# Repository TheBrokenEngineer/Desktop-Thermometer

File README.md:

# Desktop-Thermometer

A small desktop thermometer that just sits there and works. It acquires the ambient air temperature and shows the current temperature on 3 7-segment LED displays.

Designed to be low cost (under USD20) and be powered by a computer USB port, USB wall wart or power bank.

At the heart is a Microchip PIC16 microcontroller that reads the voltage produced by the sense pin on the TMP36/TMP37 sensor and shifts the converted value out to the display using 74HC595 shift registers. For full details of the device please refer to the documentation contained in the Documentation directory.

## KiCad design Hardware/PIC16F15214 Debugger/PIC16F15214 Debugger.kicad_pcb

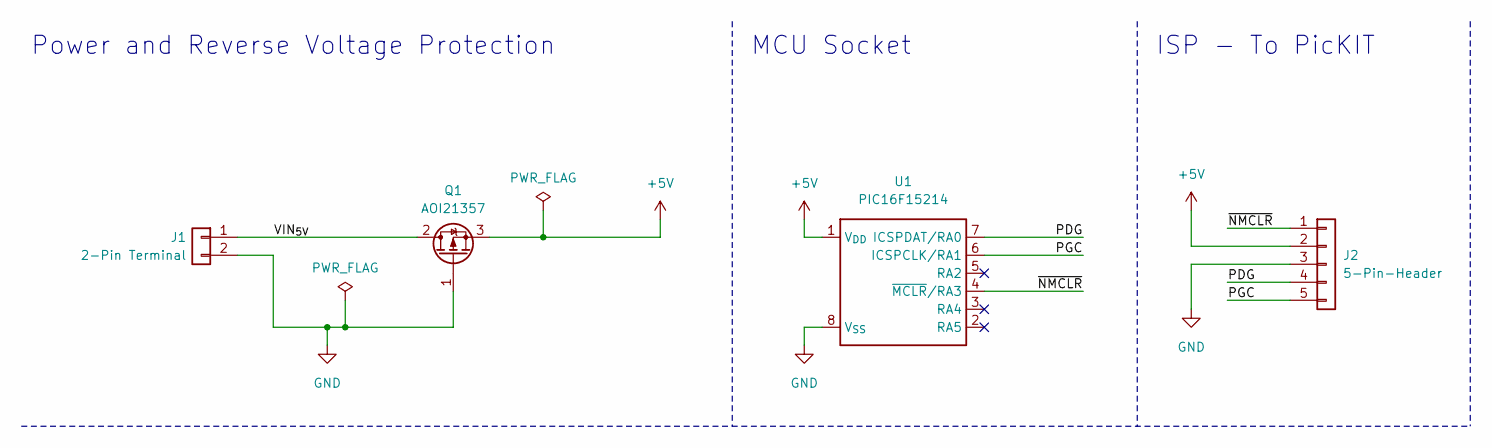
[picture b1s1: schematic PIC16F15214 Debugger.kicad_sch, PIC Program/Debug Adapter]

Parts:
J1: 2-Pin Terminal; Wurth 2 Pin Screwless Entry Wire to Board Connector
J2: 5-Pin-Header
Q1: AOI21357
U1: PIC16F15214; DIP-8_W7.62mm_Socket_Wire_Wrap

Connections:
+5V: J2.2, Q1.3 (S), U1.1 (V_{DD})
/PDG: J2.4, U1.7 (ICSPDAT/RA0)
/PGC: J2.5, U1.6 (ICSPCLK/RA1)
/VIN_{5V}: J1.1, Q1.2 (D)
/~NMCLR: J2.1, U1.4 (~MCLR/RA3)
GND: J1.2, J2.3, Q1.1 (G), U1.8 (V_{SS})

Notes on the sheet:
Power and Reverse Voltage Protection
ISP - To PicKIT
MCU Socket

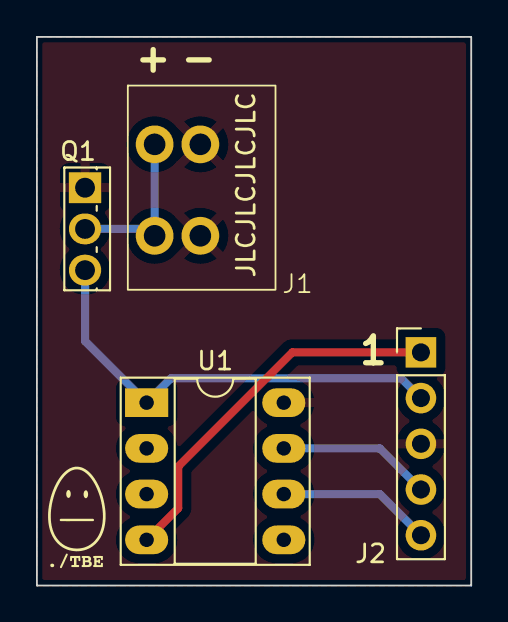
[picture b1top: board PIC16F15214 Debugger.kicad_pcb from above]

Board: 2 copper layers, 24.1 x 30.5 mm, 4 parts (0 on the bottom side), 6 nets.

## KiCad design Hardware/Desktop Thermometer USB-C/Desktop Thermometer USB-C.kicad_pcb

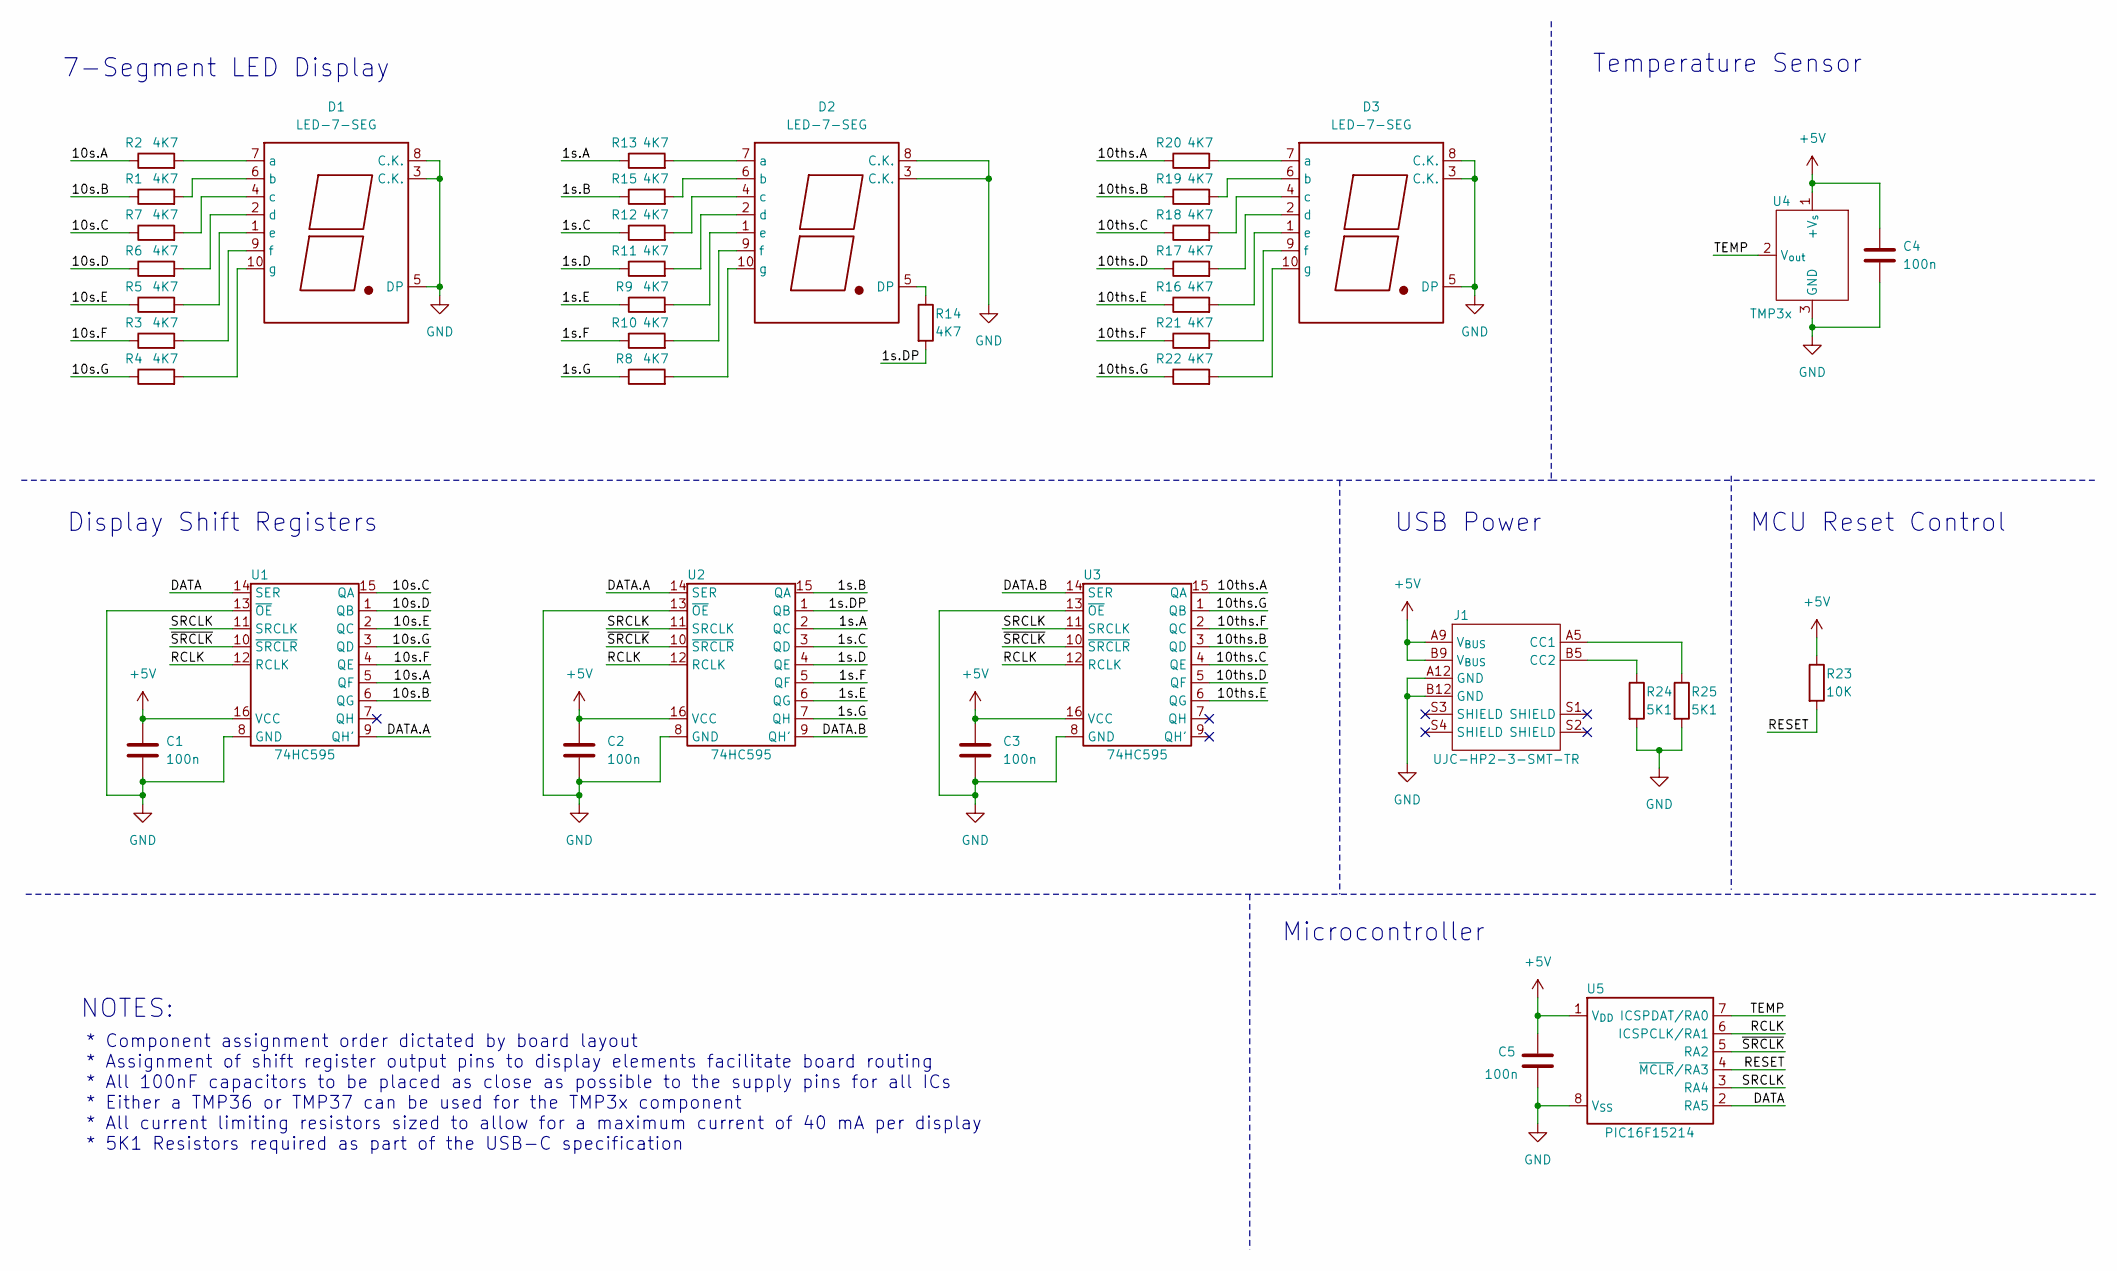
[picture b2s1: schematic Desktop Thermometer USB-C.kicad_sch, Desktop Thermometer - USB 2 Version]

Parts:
C1, C2, C3, C4, C5: 100n; C_Epoxy_D5.5mm_W3.2mm_P5.00mm
D1, D2, D3: LED-7-SEG
J1: UJC-HP2-3-SMT-TR; CUI_UJC-HP2-3-SMT-TR
R1, R2, R3, R4, R5, R6, R7, R8, R9, R10, R11, R12, R13, R14, R15, R16, R17, R18, R19, R20, R21, R22: 4K7; R_Axial_DIN0207_L6.3mm_D2.5mm_P10.16mm_Horizontal
R23: 10K; R_Axial_DIN0207_L6.3mm_D2.5mm_P10.16mm_Horizontal
R24, R25: 5K1; R_Axial_DIN0207_L6.3mm_D2.5mm_P10.16mm_Horizontal
U1, U2, U3: 74HC595; DIP-16_W7.62mm_LongPads
U4: TMP3x; TMP3x_TO-92
U5: PIC16F15214; DIP-8_W7.62mm_LongPads

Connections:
+5V: C1.1, C2.1, C3.1, C4.1, C5.1, J1.A9 (V_{BUS}), J1.B9 (V_{BUS}), R23.1, U1.16 (VCC), U2.16 (VCC), U3.16 (VCC), U4.1 (+V_{s}), U5.1 (V_{DD})
/1s.A: R13.1, U2.2 (QC)
/1s.B: R15.1, U2.15 (QA)
/1s.C: R12.1, U2.3 (QD)
/1s.D: R11.1, U2.4 (QE)
/1s.DP: R14.2, U2.1 (QB)
/1s.E: R9.1, U2.6 (QG)
/1s.F: R10.1, U2.5 (QF)
/1s.G: R8.1, U2.7 (QH)
/10s.A: R2.1, U1.5 (QF)
/10s.B: R1.1, U1.6 (QG)
/10s.C: R7.1, U1.15 (QA)
/10s.D: R6.1, U1.1 (QB)
/10s.E: R5.1, U1.2 (QC)
/10s.F: R3.1, U1.4 (QE)
/10s.G: R4.1, U1.3 (QD)
/10ths.A: R20.1, U3.15 (QA)
/10ths.B: R19.1, U3.3 (QD)
/10ths.C: R18.1, U3.4 (QE)
/10ths.D: R17.1, U3.5 (QF)
/10ths.E: R16.1, U3.6 (QG)
/10ths.F: R21.1, U3.2 (QC)
/10ths.G: R22.1, U3.1 (QB)
/DATA: U1.14 (SER), U5.2 (RA5)
/DATA.A: U1.9 (QH'), U2.14 (SER)
/DATA.B: U2.9 (QH'), U3.14 (SER)
/RCLK: U1.12 (RCLK), U2.12 (RCLK), U3.12 (RCLK), U5.6 (ICSPCLK/RA1)
/RESET: R23.2, U5.4 (~MCLR/RA3)
/SRCLK: U1.11 (SRCLK), U2.11 (SRCLK), U3.11 (SRCLK), U5.3 (RA4)
/TEMP: U4.2 (V_{out}), U5.7 (ICSPDAT/RA0)
/~SRCLK: U1.10 (~SRCLR), U2.10 (~SRCLR), U3.10 (~SRCLR), U5.5 (RA2)
GND: C1.2, C2.2, C3.2, C4.2, C5.2, D1.3 (C.K.), D1.5 (DP), D1.8 (C.K.), D2.3 (C.K.), D2.8 (C.K.), D3.3 (C.K.), D3.5 (DP), D3.8 (C.K.), J1.A12 (GND), J1.B12 (GND), R24.2, R25.2, U1.8 (GND), U1.13 (~OE), U2.8 (GND), U2.13 (~OE), U3.8 (GND), U3.13 (~OE), U4.3 (GND), U5.8 (V_{SS})
unnamed: D1.7 (a), R2.2
unnamed: D1.6 (b), R1.2
unnamed: D1.4 (c), R7.2
unnamed: D1.2 (d), R6.2
unnamed: D1.1 (e), R5.2
unnamed: D1.9 (f), R3.2
unnamed: D1.10 (g), R4.2
unnamed: D2.5 (DP), R14.1
unnamed: D2.7 (a), R13.2
unnamed: D2.6 (b), R15.2
unnamed: D2.4 (c), R12.2
unnamed: D2.2 (d), R11.2
unnamed: D2.1 (e), R9.2
unnamed: D2.9 (f), R10.2
unnamed: D2.10 (g), R8.2
unnamed: D3.7 (a), R20.2
unnamed: D3.6 (b), R19.2
unnamed: D3.4 (c), R18.2
unnamed: D3.2 (d), R17.2
unnamed: D3.1 (e), R16.2
unnamed: D3.9 (f), R21.2
unnamed: D3.10 (g), R22.2
unnamed: J1.A5 (CC1), R25.1
unnamed: J1.B5 (CC2), R24.1

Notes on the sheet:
Microcontroller
Temperature Sensor
USB Power
* Component assignment order dictated by board layout * Assignment of shift register output pins to display elements facilitate board routing * All 100nF capacitors to be placed as close as possible to the supply pins for all ICs * Either a TMP36 or TMP37 can be used for the TMP3x component * All c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
Display Shift Registers
NOTES:
7-Segment LED Display
MCU Reset Control

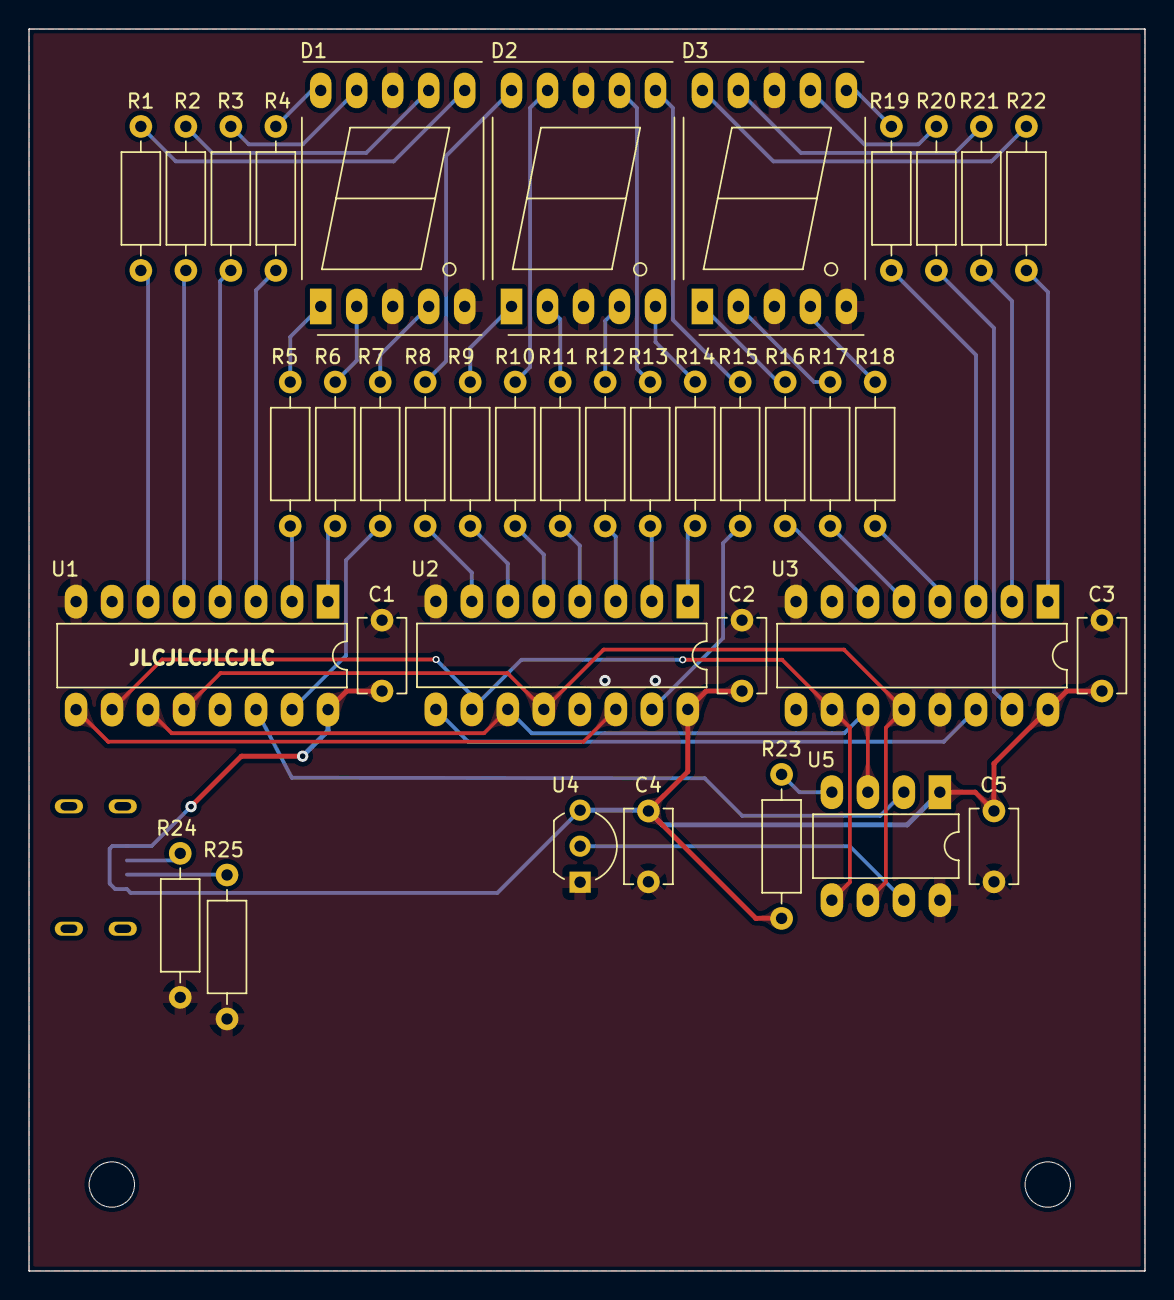
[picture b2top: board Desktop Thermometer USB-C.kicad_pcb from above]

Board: 2 copper layers, 78.7 x 87.6 mm, 39 parts (1 on the bottom side), 56 nets.

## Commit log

2024-02-05 Update the readme
2024-02-05 Add in data sheets and directory structure
2024-02-05 Created basic hardware schematic and models
2024-02-05 Updated some symbols and footprints. Also added a new model for an epoxy type ceramic capacitor
2024-02-05 Schematic roughed out, requires a tidy up into sections. Added some more symbols and footprints...Hopefully done with that stuff!
2024-02-05 Initial attempt of PCB layout
2024-02-06 Traces added, still have some thermal relief issues that require investigation
2024-02-06 Make the schematic pretty and create the USB-C variant of the hardware.
2024-02-06 Updated the USB-C version of the schematic and updated the board to reflect changes
2024-02-06 Update licenses for hardware and software
2024-02-06 Initial firmware version
2024-02-06 Managed to get the footprint for the TMP3x device around the wrong way, this is now fixed. Also included data sheets for the PIC programmer and updates to the code configuration after testing.
2024-02-06 Add in code for using the TMP37 instead of the TMP36. A simple compile time definition.
2024-02-08 Finished PCB routing and generated GERBERS for both versions of the hardware.
2024-02-09 Created the debugger/programmer. Also generated the PCB gerber files for submission to the FAB house
2024-02-15 Created PDF versions of the schematic diagrams
2024-02-15 File rename
2024-02-15 Updated some documentation
2024-02-22 Updated documentation and build for the firmware
2024-02-27 Final Version, project finished
2024-02-28 Release time!

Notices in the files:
Hardware/Desktop Thermometer USB-C/Desktop Thermometer USB-C.kicad_pcb:
Copyright © 2024 - The Broken Engineer
Licensed under CERN-OHL-2 v2
